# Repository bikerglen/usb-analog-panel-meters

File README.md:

# usb-analog-panel-meters

See https://bikerglen.com/blog/building-usb-analog-panel-meters/ for a description of the boards and software available in this repository.

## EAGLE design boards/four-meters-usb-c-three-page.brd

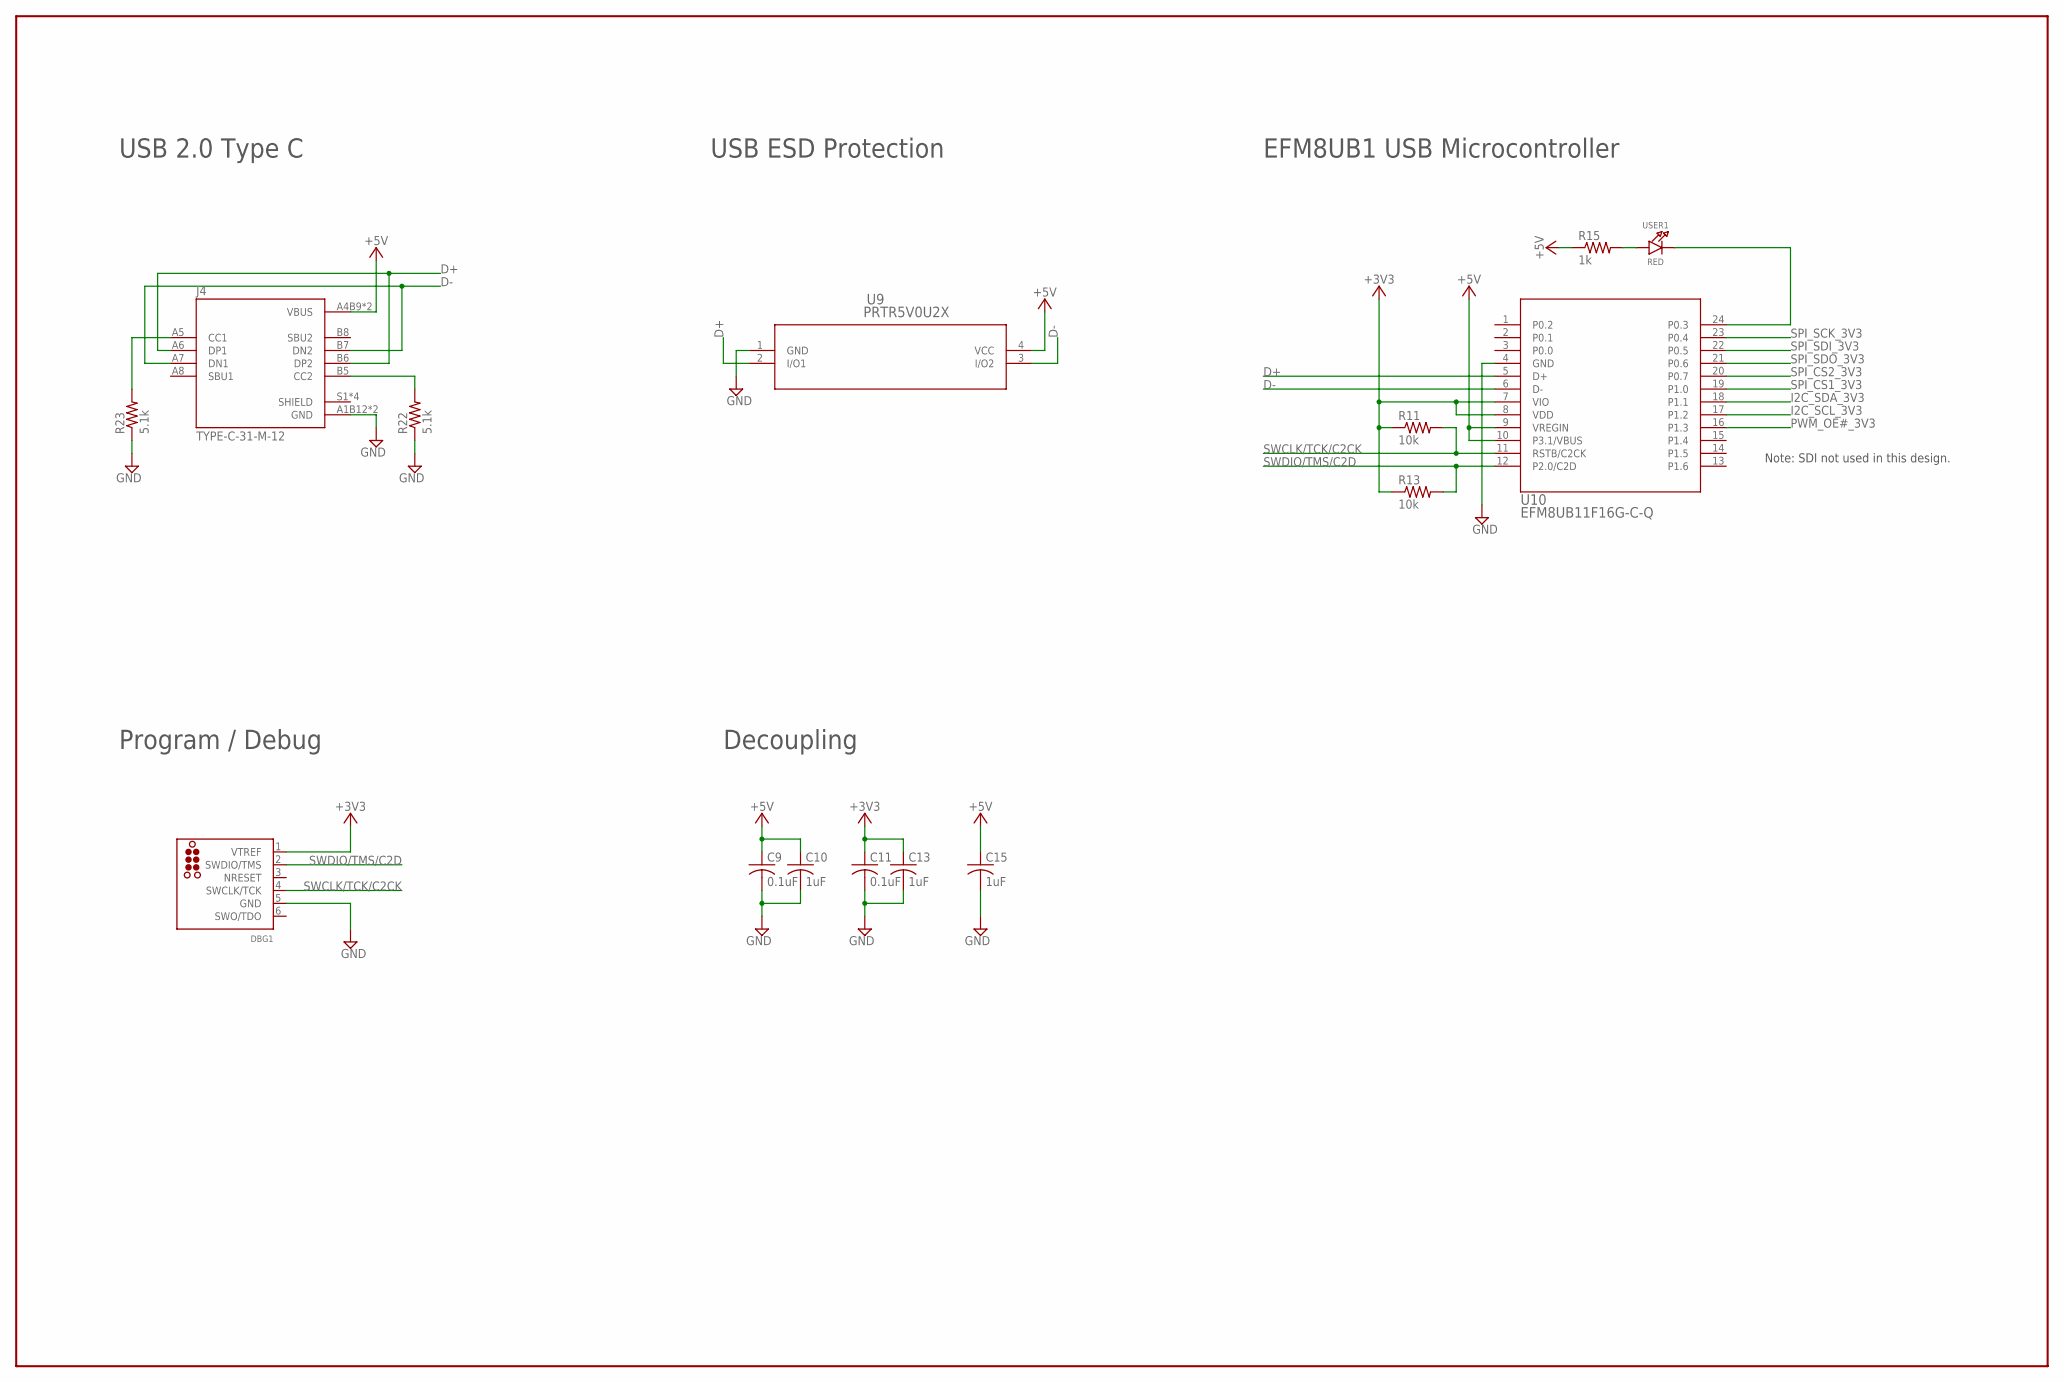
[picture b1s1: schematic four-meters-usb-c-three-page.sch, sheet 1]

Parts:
C9, C11: 0.1uF; C0603
C10, C13: 1uF; C0603
C15: 1uF; C1210K
DBG1: TC2030-CTX-SWD; TC2030-MCP-NL
J4: TYPE-C-31-M-12; HRO_TYPE-C-31-M-12
R11, R13: 10k; R0603
R15: 1k; R0603
R22, R23: 5.1k; R0603
U9: PRTR5V0U2X; SOT143B
U10: EFM8UB11F16G-C-Q; QSOP24
USER1: RED; CHIPLED_0805_NOOUTLINE

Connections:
+3V3: C11.1, C13.1, DBG1.1 (VTREF), R11.1, R13.1, U10.7 (VIO), U10.8 (VDD); also elsewhere on the board
+5V: C9.1, C10.1, C15.1, J4.A4B9 (VBUS), J4.B4A9 (VBUS), R15.1, U9.4 (VCC), U10.9 (VREGIN), U10.10 (P3.1/VBUS); also elsewhere on the board
D+: J4.A6 (DP1), J4.B6 (DP2), U9.2 (I/O1), U10.5 (D+)
D-: J4.A7 (DN1), J4.B7 (DN2), U9.3 (I/O2), U10.6 (D-)
GND: C9.2, C10.2, C11.2, C13.2, C15.2, DBG1.5 (GND), J4.A1B12 (GND), J4.B1A12 (GND), R22.1, R23.1, U9.1 (GND), U10.4 (GND); also elsewhere on the board
I2C_SCL_3V3: U10.17 (P1.2); also elsewhere on the board
I2C_SDA_3V3: U10.18 (P1.1); also elsewhere on the board
LED1: U10.24 (P0.3), USER1.C
unnamed: R15.2, USER1.A
unnamed: J4.B5 (CC2), R22.2
unnamed: J4.A5 (CC1), R23.2
NRESET: DBG1.3 (NRESET)
PWM_OE#_3V3: U10.16 (P1.3); also elsewhere on the board
SPI_CS1_3V3: U10.19 (P1.0); also elsewhere on the board
SPI_CS2_3V3: U10.20 (P0.7); also elsewhere on the board
SPI_SCK_3V3: U10.23 (P0.4); also elsewhere on the board
SPI_SDI_3V3: U10.22 (P0.5)
SPI_SDO_3V3: U10.21 (P0.6); also elsewhere on the board
SWCLK/TCK/C2CK: DBG1.4 (SWCLK/TCK), R11.2, U10.11 (RSTB/C2CK)
SWDIO/TMS/C2D: DBG1.2 (SWDIO/TMS), R13.2, U10.12 (P2.0/C2D)

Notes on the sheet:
USB 2.0 Type C
USB ESD Protection
EFM8UB1 USB Microcontroller
Program / Debug
Decoupling
Note: SDI not used in this design.

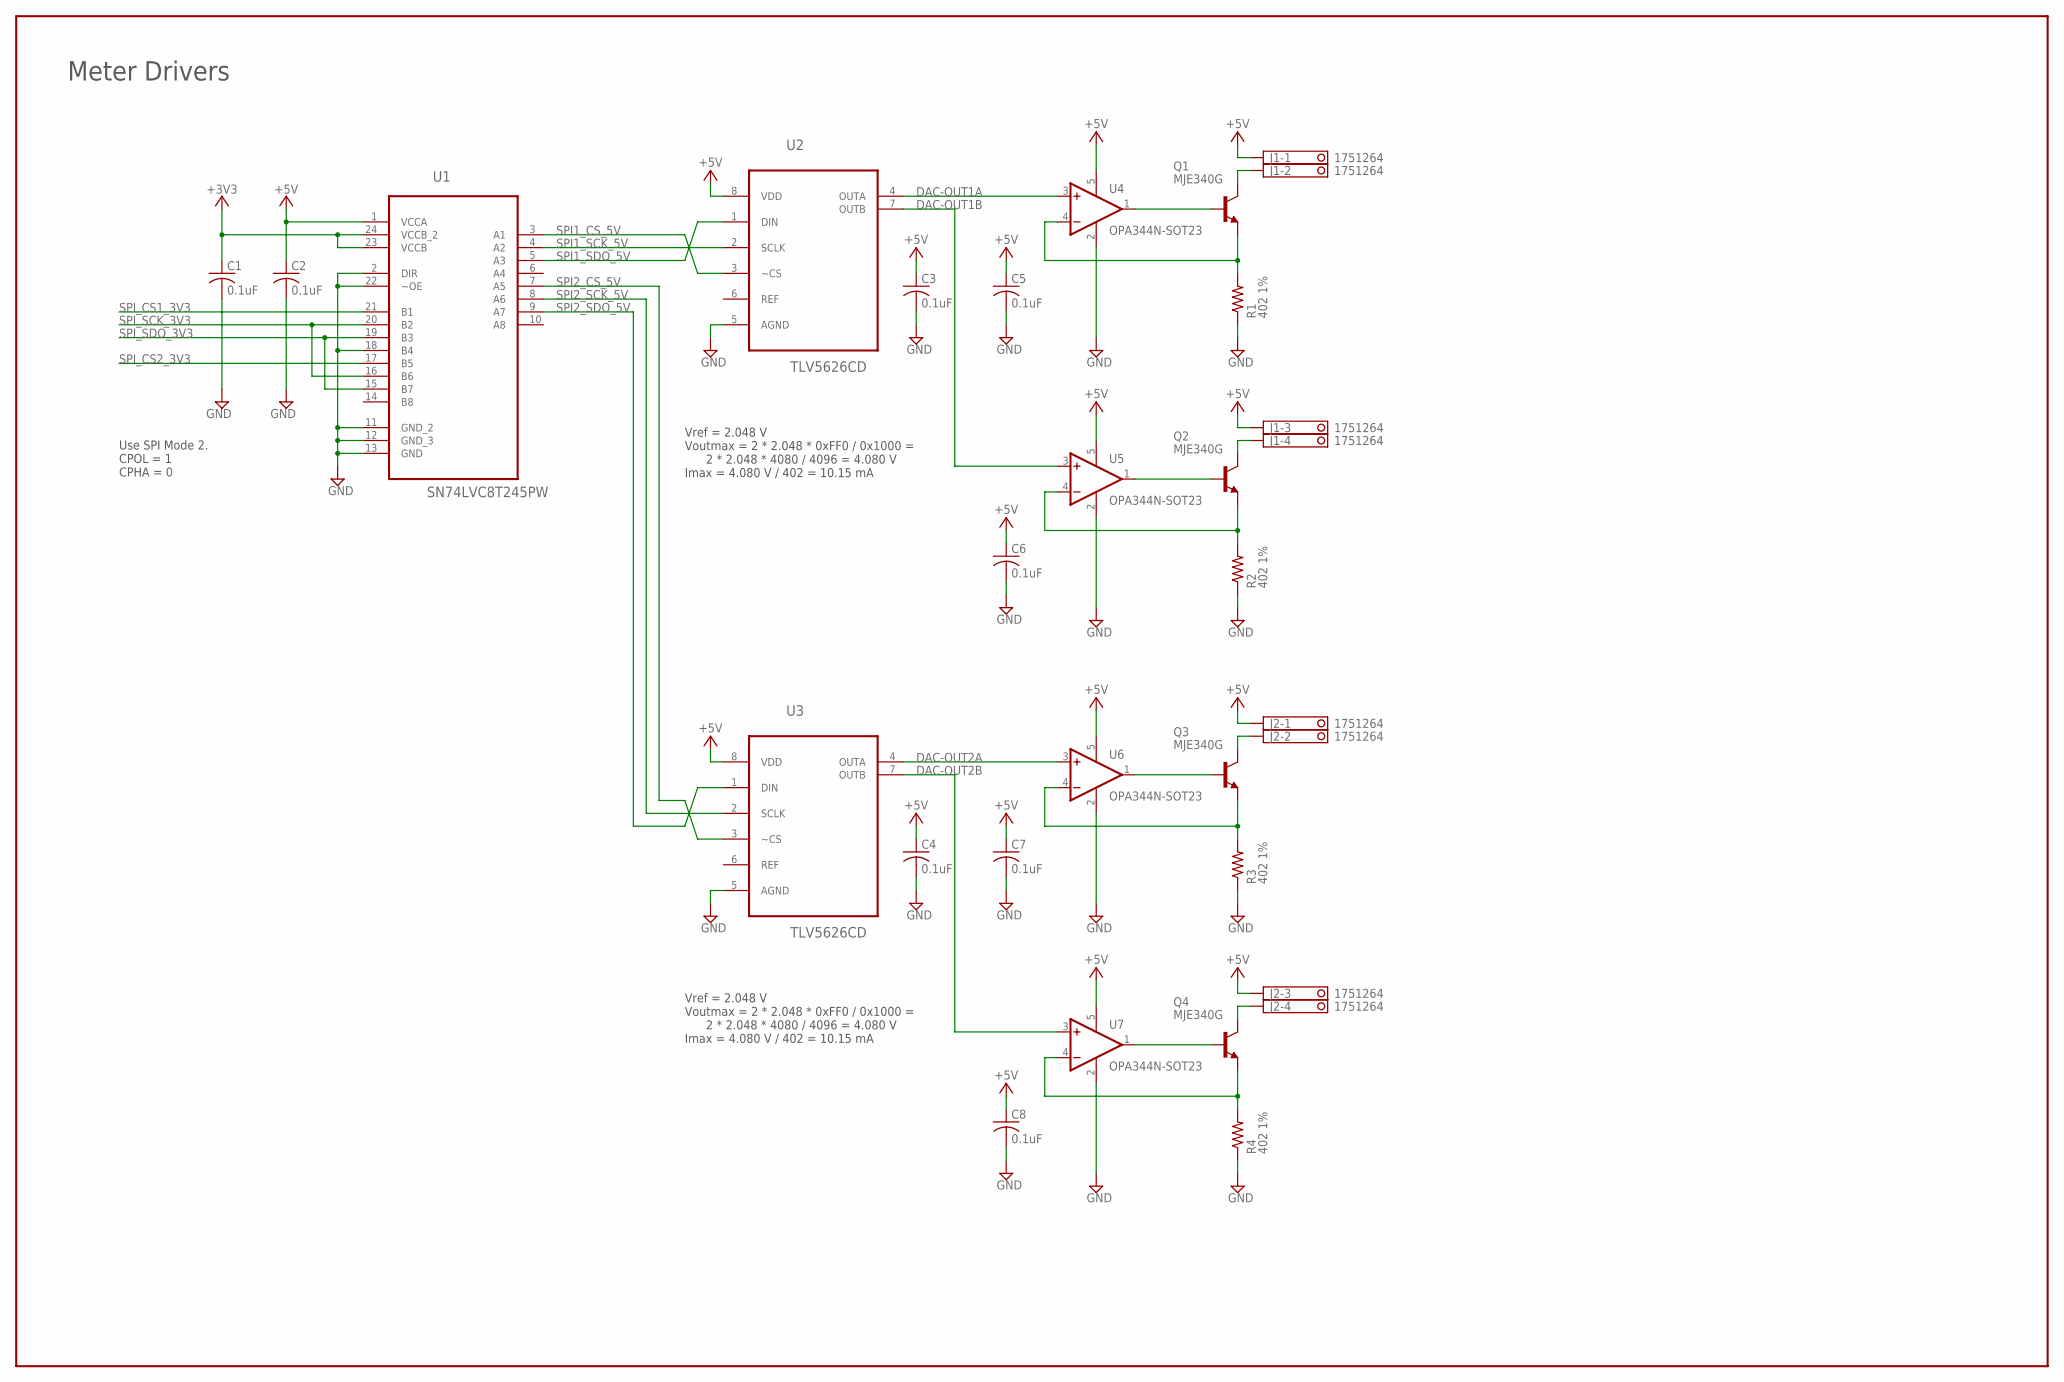
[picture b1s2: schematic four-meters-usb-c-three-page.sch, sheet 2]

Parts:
C1, C2, C3, C4, C5, C6, C7, C8: 0.1uF; C0603K; MFR_PART_NO C1206C104K5RACAUTO
J1, J2: 1751264
Q1, Q2, Q3, Q4: MJE340G; TO126V; MFR_PART_NO MJE340G
R1, R2, R3, R4: 402 1%; R1210; MFR_PART_NO ERJ-14NF73R2U
U1: SN74LVC8T245PW; SOP65P640X120-24N; MFR_PART_NO SN74LVC8T245PW
U2, U3: TLV5626CD; SOIC127P600X175-8N; MFR_PART_NO TLV5626CD
U4, U5, U6, U7: OPA344N-SOT23; SOT23-5; MFR_PART_NO OPA344NA/3K

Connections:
+3V3: C1.1, U1.23 (VCCB), U1.24 (VCCB_2); also elsewhere on the board
+5V: C2.1, C3.1, C4.1, C5.1, C6.1, C7.1, C8.1, J1.1, J1.3, J2.1, J2.3, U1.1 (VCCA), U2.8 (VDD), U3.8 (VDD), U4.5 (V+), U5.5 (V+), U6.5 (V+), U7.5 (V+); also elsewhere on the board
DAC-OUT1A: U2.4 (OUTA), U4.3 (+IN)
DAC-OUT1B: U2.7 (OUTB), U5.3 (+IN)
DAC-OUT2A: U3.4 (OUTA), U6.3 (+IN)
DAC-OUT2B: U3.7 (OUTB), U7.3 (+IN)
GND: C1.2, C2.2, C3.2, C4.2, C5.2, C6.2, C7.2, C8.2, R1.1, R2.1, R3.1, R4.1, U1.2 (DIR), U1.11 (GND_2), U1.12 (GND_3), U1.13 (GND), U1.18 (B4), U1.22 (~OE), U2.5 (AGND), U3.5 (AGND), U4.2 (V-), U5.2 (V-), U6.2 (V-), U7.2 (V-); also elsewhere on the board
unnamed: Q1.1 (E), R1.2, U4.4 (-IN)
unnamed: Q3.1 (E), R3.2, U6.4 (-IN)
unnamed: Q1.3 (B), U4.1 (OUT)
unnamed: Q3.3 (B), U6.1 (OUT)
unnamed: Q4.1 (E), R4.2, U7.4 (-IN)
unnamed: Q4.3 (B), U7.1 (OUT)
unnamed: Q2.1 (E), R2.2, U5.4 (-IN)
unnamed: Q2.3 (B), U5.1 (OUT)
OUT1A: J1.2, Q1.2 (C)
OUT1B: J1.4, Q2.2 (C)
OUT2A: J2.2, Q3.2 (C)
OUT2B: J2.4, Q4.2 (C)
SPI1_CS_5V: U1.3 (A1), U2.3 (~CS)
SPI1_SCK_5V: U1.4 (A2), U2.2 (SCLK)
SPI1_SDO_5V: U1.5 (A3), U2.1 (DIN)
SPI2_CS_5V: U1.7 (A5), U3.3 (~CS)
SPI2_SCK_5V: U1.8 (A6), U3.2 (SCLK)
SPI2_SDO_5V: U1.9 (A7), U3.1 (DIN)
SPI_CS1_3V3: U1.21 (B1); also elsewhere on the board
SPI_CS2_3V3: U1.17 (B5); also elsewhere on the board
SPI_SCK_3V3: U1.16 (B6), U1.20 (B2); also elsewhere on the board
SPI_SDO_3V3: U1.15 (B7), U1.19 (B3); also elsewhere on the board

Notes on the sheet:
Vref = 2.048 V Voutmax = 2 * 2.048 * 0xFF0 / 0x1000 = 2 * 2.048 * 4080 / 4096 = 4.080 V Imax = 4.080 V / 402 = 10.15 mA
Use SPI Mode 2. CPOL = 1 CPHA = 0
Meter Drivers

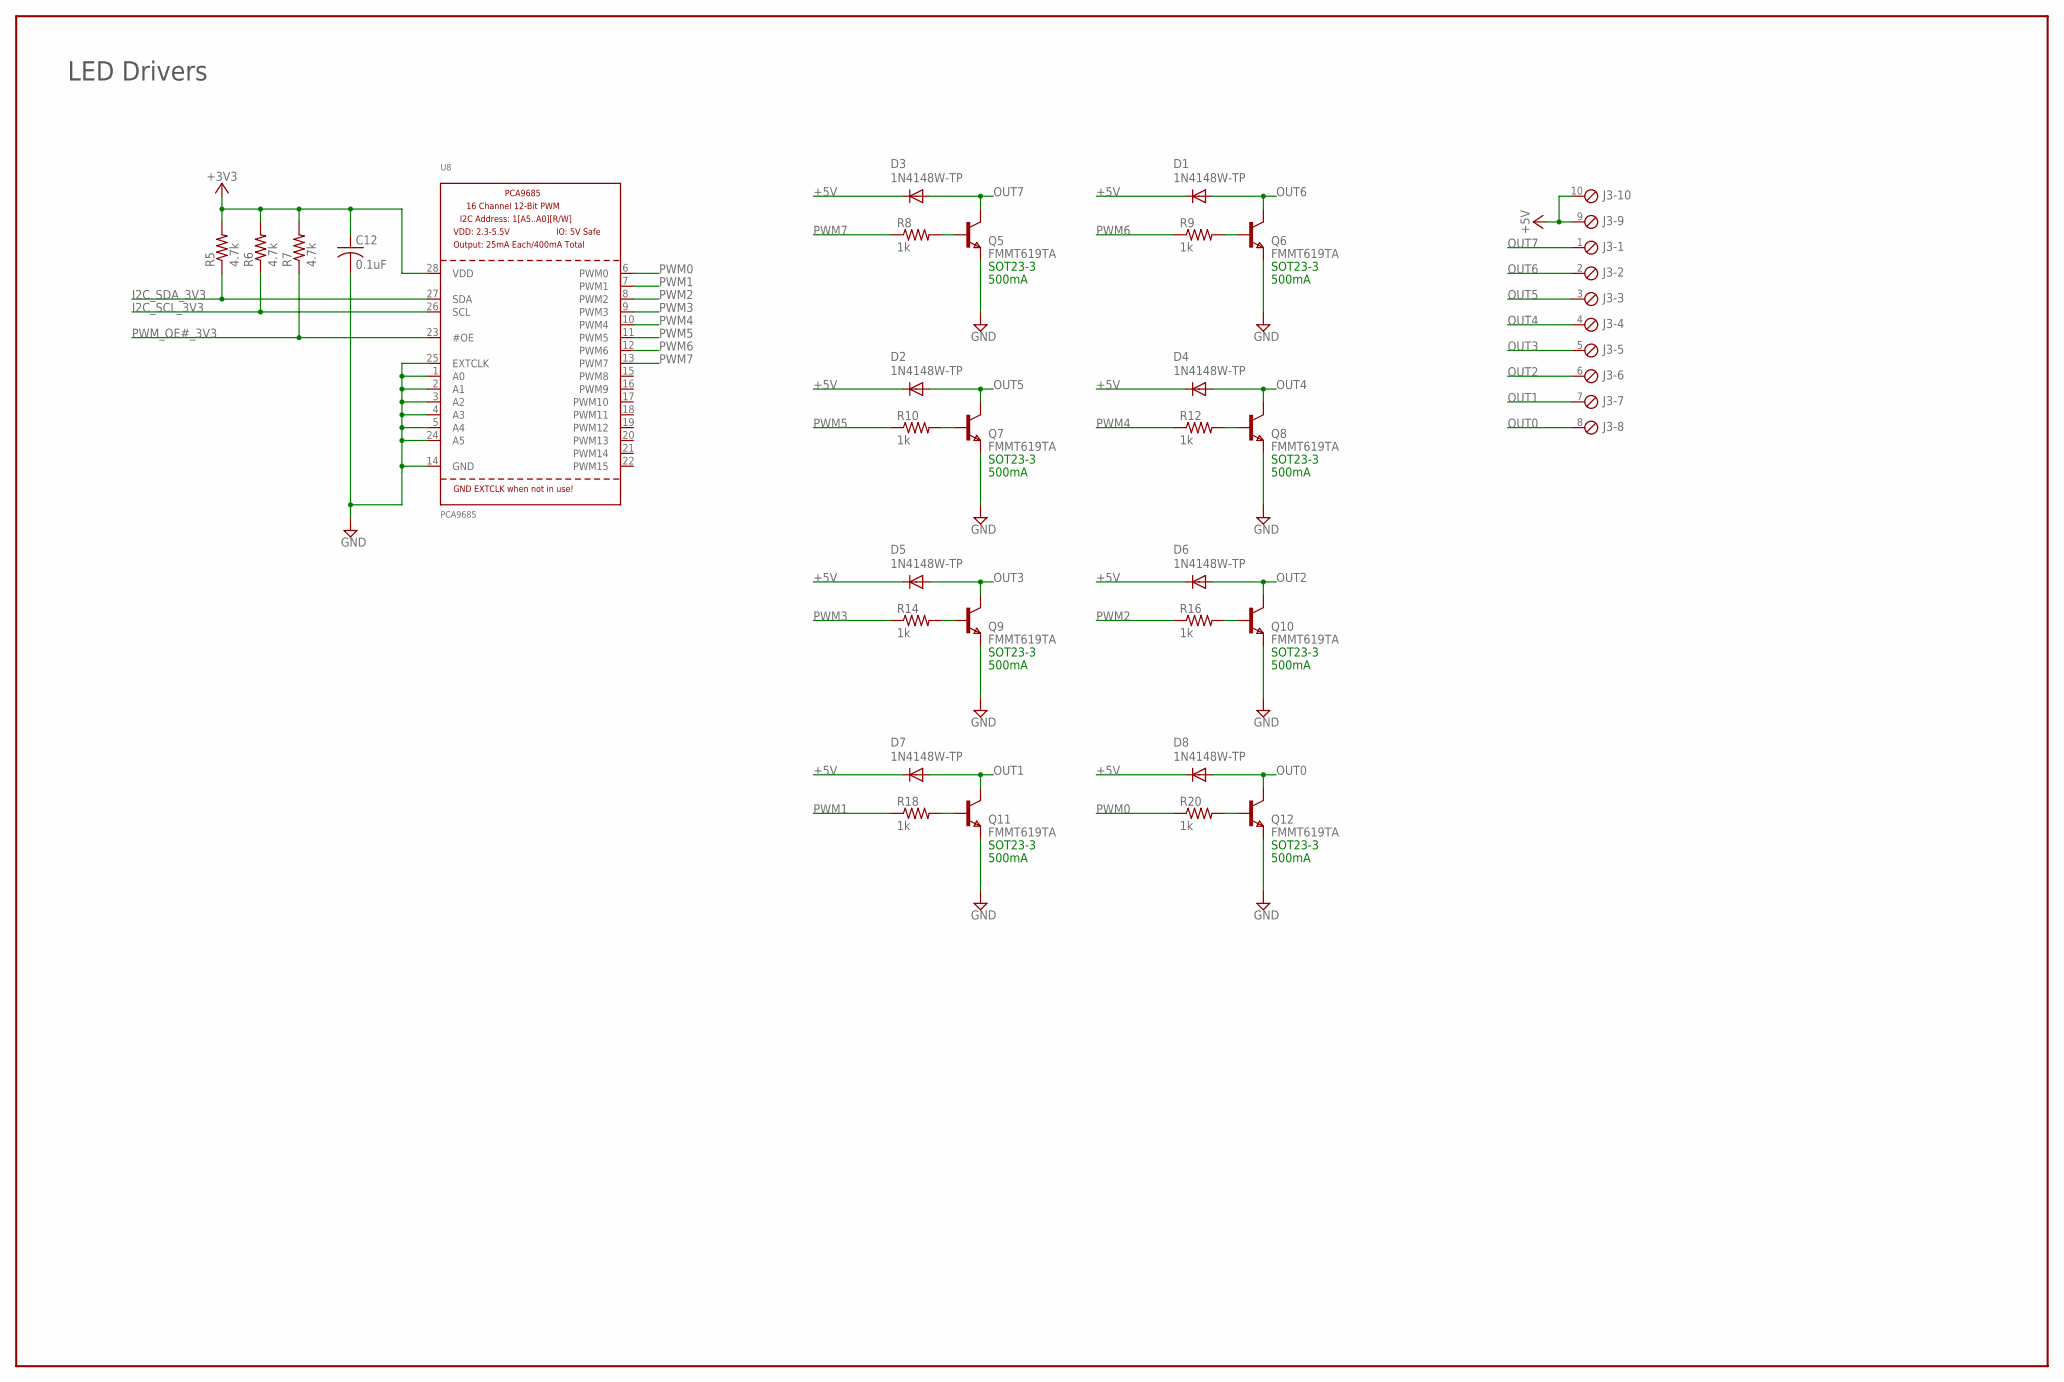
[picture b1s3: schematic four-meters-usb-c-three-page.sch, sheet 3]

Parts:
C12: 0.1uF; C0603K; MFR_PART_NO C1206C104K5RACAUTO
D1, D2, D3, D4, D5, D6, D7, D8: 1N4148W-TP; SOD123
J3: MPT10; 10POL254
Q5, Q6, Q7, Q8, Q9, Q10, Q11, Q12: FMMT619TA; SOT-23
R5, R6, R7: 4.7k; R0603
R8, R9, R10, R12, R14, R16, R18, R20: 1k; R0603
U8: PCA9685; TSSOP28

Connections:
+3V3: C12.1, R5.2, R6.2, R7.2, U8.28 (VDD); also elsewhere on the board
+5V: D1.C, D2.C, D3.C, D4.C, D5.C, D6.C, D7.C, D8.C, J3.9, J3.10; also elsewhere on the board
GND: C12.2, Q5.2 (E), Q6.2 (E), Q7.2 (E), Q8.2 (E), Q9.2 (E), Q10.2 (E), Q11.2 (E), Q12.2 (E), U8.1 (A0), U8.2 (A1), U8.3 (A2), U8.4 (A3), U8.5 (A4), U8.14 (GND), U8.24 (A5), U8.25 (EXTCLK); also elsewhere on the board
I2C_SCL_3V3: R6.1, U8.26 (SCL); also elsewhere on the board
I2C_SDA_3V3: R5.1, U8.27 (SDA); also elsewhere on the board
unnamed: Q6.3 (B), R9.2
unnamed: Q7.3 (B), R10.2
unnamed: Q8.3 (B), R12.2
unnamed: Q9.3 (B), R14.2
unnamed: Q10.3 (B), R16.2
unnamed: Q11.3 (B), R18.2
unnamed: Q12.3 (B), R20.2
unnamed: Q5.3 (B), R8.2
OUT0: D8.A, J3.8, Q12.1 (C)
OUT1: D7.A, J3.7, Q11.1 (C)
OUT2: D6.A, J3.6, Q10.1 (C)
OUT3: D5.A, J3.5, Q9.1 (C)
OUT4: D4.A, J3.4, Q8.1 (C)
OUT5: D2.A, J3.3, Q7.1 (C)
OUT6: D1.A, J3.2, Q6.1 (C)
OUT7: D3.A, J3.1, Q5.1 (C)
PWM0: R20.1, U8.6 (PWM0)
PWM1: R18.1, U8.7 (PWM1)
PWM2: R16.1, U8.8 (PWM2)
PWM3: R14.1, U8.9 (PWM3)
PWM4: R12.1, U8.10 (PWM4)
PWM5: R10.1, U8.11 (PWM5)
PWM6: R9.1, U8.12 (PWM6)
PWM7: R8.1, U8.13 (PWM7)
PWM_OE#_3V3: R7.1, U8.23 (#OE); also elsewhere on the board

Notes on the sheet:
SOT23-3
500mA
LED Drivers

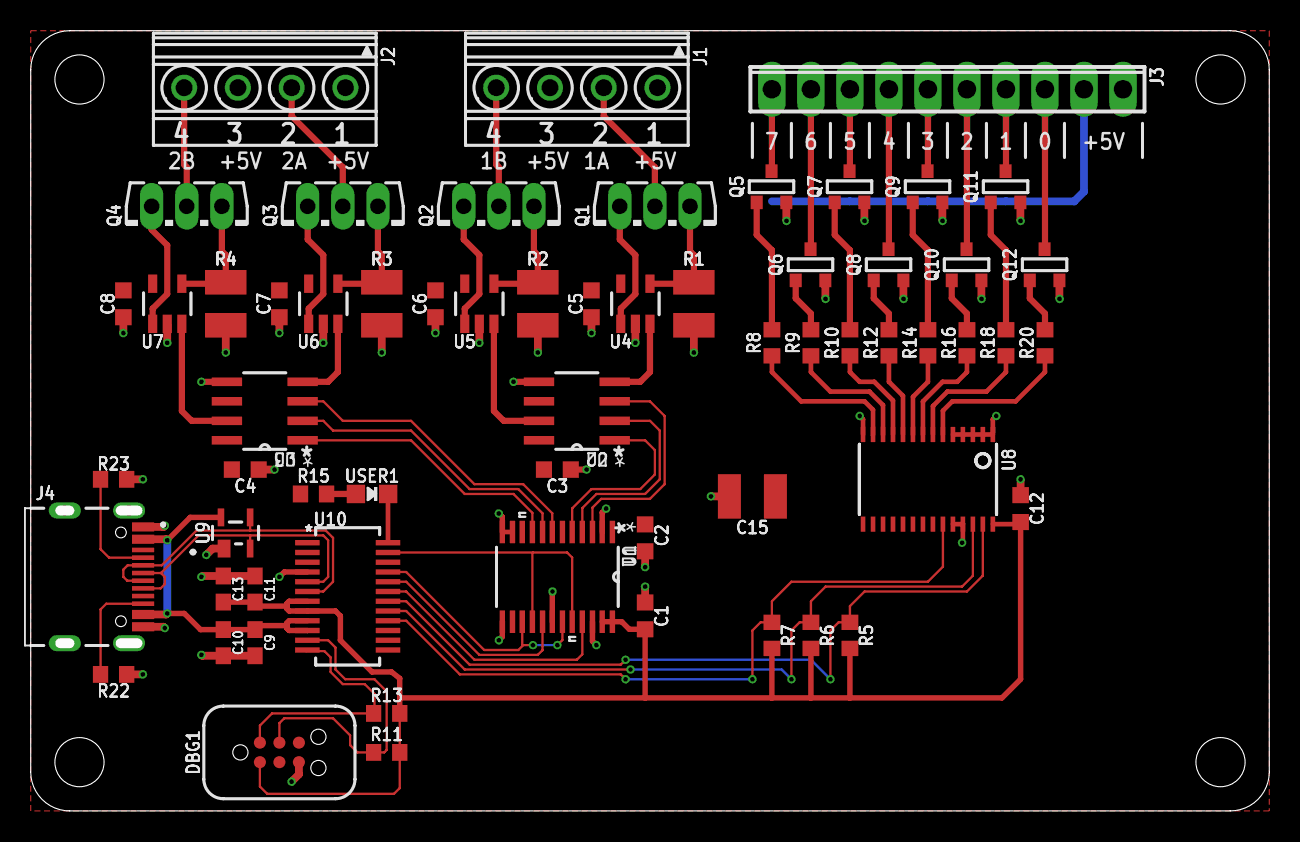
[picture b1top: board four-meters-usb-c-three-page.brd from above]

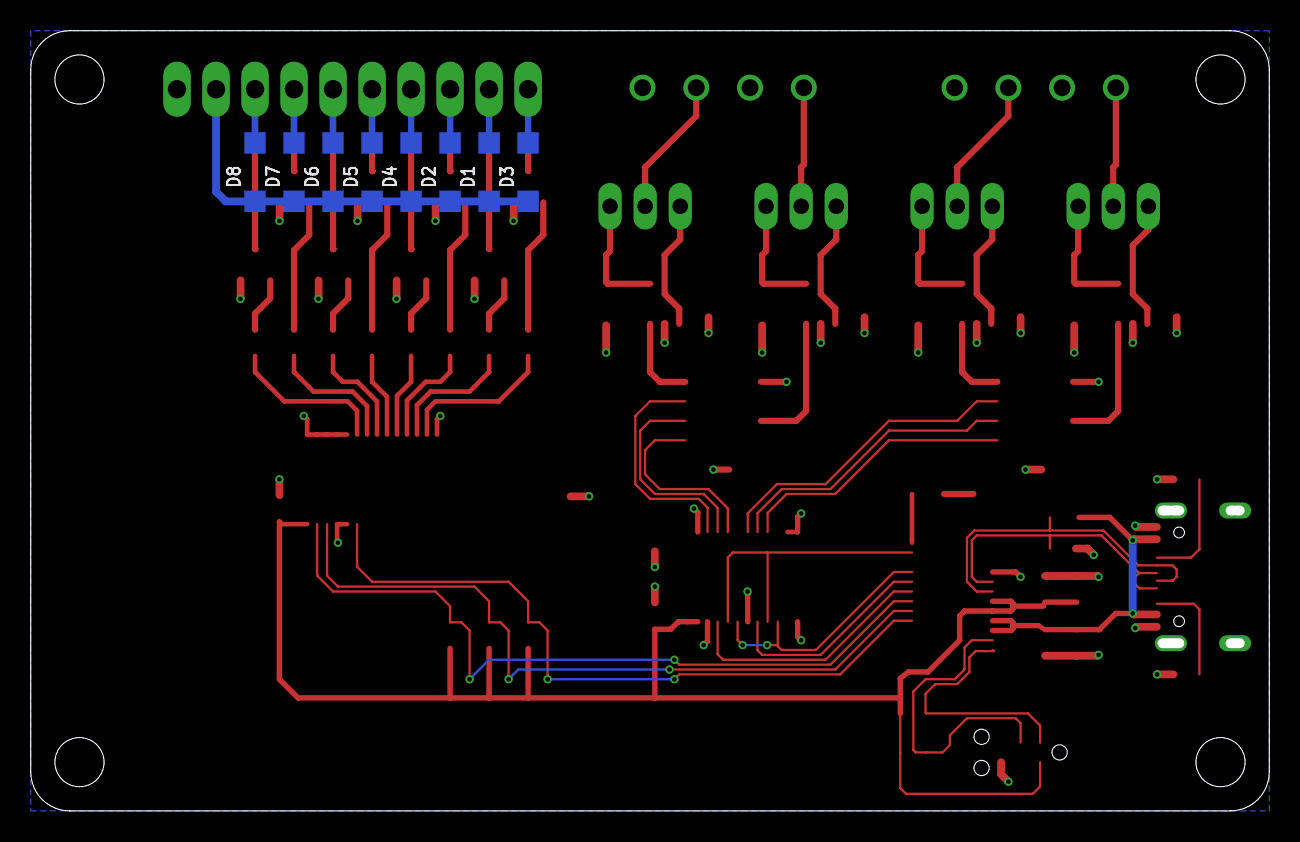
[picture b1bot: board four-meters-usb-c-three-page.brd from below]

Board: 2 copper layers, 80.0 x 50.1 mm, 70 parts (8 on the bottom side), 64 nets.

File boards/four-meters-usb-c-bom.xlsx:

Qty | Parts | Description | Mfr | Mfr Part # | Dist | Dist Part #
11 | C1, C2, C3, C4, C5, C6, C7, C8, C9, C11, C12 | CAP CER 0.1UF 50V X7R 0603 | KEMET | C0603C104K5RACTU | Digi-Key | 399-5089-1-ND
2 | C10, C13 | CAP CER 1UF 16V X7R 0603 | KEMET | C0603C105K4RACTU | Digi-Key | 399-7847-1-ND
1 | C15 | CAP CER 1UF 25V X7R 1210 | KEMET | C1210C105K3RACTU | Digi-Key | 399-8220-1-ND
8 | D1, D2, D3, D4, D5, D6, D7, D8 | DIODE GEN PURP 100V 150MA SOD123 | Micro Commercial Co | 1N4148W-TP | Digi-Key | 1N4148WTPMSCT-ND
2 | J1, J2 | TERM BLK 4POS SIDE ENT 3.5MM PCB | Phoenix Contact | 1751264 | Digi-Key | 277-5744-ND
1 | J3 | TERM BLK 10P SIDE ENT 2.54MM PCB | On Shore Technology Inc. | OSTVN10A150 | Digi-Key | ED10567-ND
1 | J4 | CONN RCPT USB2.0 TYPEC 5A | GCT | USB4105-GF-A | Digi-Key | 2073-USB4105-GF-ACT-ND
4 | Q1, Q2, Q3, Q4 | TRANS NPN 300V 0.5A TO225AA | ON Semiconductor | MJE340G | Digi-Key | MJE340GOS-ND
8 | Q5, Q6, Q7, Q8, Q9, Q10, Q11, Q12 | TRANS NPN 50V 2A SOT23-3 | Diodes Incorporated | FMMT619TA | Digi-Key | FMMT619CT-ND
4 | R1, R2, R3, R4 | RES SMD 402 OHM 1% 1/2W 1210 | Vishay Dale | CRCW1210402RFKEA | Digi-Key | 541-402AACT-ND
9 | R8, R9, R10, R12, R14, R15, R16, R18, R20 | RES SMD 1K OHM 5% 1/10W 0603 | Panasonic Electronic Components | ERJ-3GEYJ102V | Digi-Key | P1.0KGCT-ND
3 | R5, R6, R7 | RES SMD 4.7K OHM 5% 1/10W 0603 | Panasonic Electronic Components | ERJ-3GEYJ472V | Digi-Key | P4.7KGCT-ND
2 | R11, R13 | RES SMD 10K OHM 5% 1/10W 0603 | Panasonic Electronic Components | ERJ-3GEYJ103V | Digi-Key | P10KGCT-ND
2 | R22, R23 | RES SMD 5.1K OHM 5% 1/10W 0603 | Panasonic Electronic Components | ERJ-3GEYJ512V | Digi-Key | P5.1KGCT-ND
1 | U1 | IC TRNSLTR BIDIRECTIONAL 24TSSOP | Texas Instruments | SN74LVC8T245PW | Digi-Key | 296-34079-5-ND
2 | U2, U3 | IC DAC 8BIT V-OUT 8SOIC | Texas Instruments | TLV5626CD | Digi-Key | 296-2311-5-ND
4 | U4, U5, U6, U7 | IC OPAMP GP 1 CIRCUIT SOT23-5 | Texas Instruments | OPA344NA/3K | Digi-Key | 296-41475-1-ND
1 | U8 | IC LED DRVR LIN DIM 25MA 28TSSOP | NXP USA Inc. | PCA9685PW,118 | Digi-Key | 568-11925-1-ND
1 | U9 | TVS DIODE 5.5V SOT143B | Nexperia USA Inc. | PRTR5V0U2X,215 | Digi-Key | 1727-3884-1-ND
1 | U10 | IC MCU 8BIT 16KB FLASH 24QSOP | Silicon Labs | EFM8UB11F16G-C-QSOP24 | Digi-Key | 336-3411-5-ND
1 | D1 | LED GREEN CLEAR CHIP SMD | Kingbright | APHCM2012CGCK-F01 | Digi-Key | 754-1094-1-ND
4 | --- | HUA SO45 10mA Panel Meter | HUA | --- | eBay/AliExpress | ---
 |  |  |  |  |  |  |  |  |  |  |  |  |  |  |  |  |  |  |  |  |  |  |  | Texas Instruments
 |  |  |  |  |  |  |  |  |  |  |  |  |  |  |  |  |  |  |  |  |  |  |  | Texas Instruments
 |  |  |  |  |  |  |  |  |  |  |  |  |  |  |  |  |  |  |  |  |  |  |  | Texas Instruments
 |  |  |  |  |  |  |  |  |  |  |  |  |  |  |  |  |  |  |  |  |  |  |  |  | NXP
 |  |  |  |  |  |  |  |  |  |  |  |  |  |  |  |  |  |  |  |  |  |  |  |  | Silicon Labs

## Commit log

2020-11-02 initial checkin
2020-11-03 added 34461A lxi/scpi current measurement code
2020-11-26 Update README.md
    add link to blog post

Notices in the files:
parts and their libraries:
tag-connect: ©2009 ROFA.cz - modified and updated by Robert Darlington ‹rdarlington@gmail.com›
